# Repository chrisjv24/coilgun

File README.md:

# coilgun
This repository will contain all design files and documentation concerning the Carter X Chris coilgun design.

## Repo Architecture
The repo will be split into the four subsystems of chassis, propulsion, controls, and safety, along with an additional directory for non-technical documents.

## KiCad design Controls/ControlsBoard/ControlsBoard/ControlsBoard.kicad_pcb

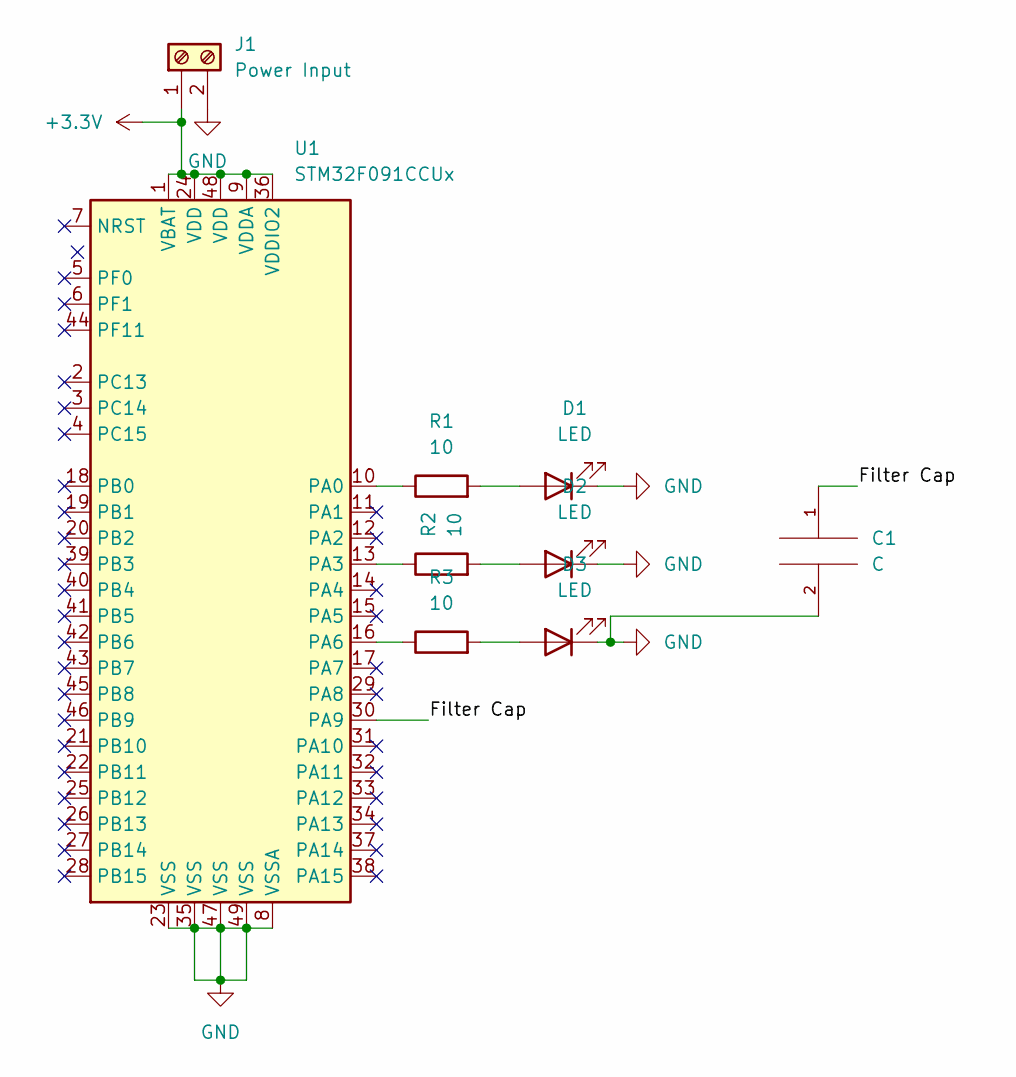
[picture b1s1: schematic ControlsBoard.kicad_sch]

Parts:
C1: C; C_0603_1608Metric
D1, D2, D3: LED; LED_0603_1608Metric
J1: Power Input; TerminalBlock_4Ucon_1x08_P3.50mm_Horizontal
R1, R2: 10; R_0805_2012Metric
R3: 10; R_Axial_DIN0207_L6.3mm_D2.5mm_P2.54mm_Vertical
U1: STM32F091CCUx; QFN-48-1EP_7x7mm_P0.5mm_EP5.6x5.6mm

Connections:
+3.3V: J1.1, U1.1 (VBAT), U1.9 (VDDA), U1.24 (VDD), U1.36 (VDDIO2), U1.48 (VDD)
/Filter Cap: C1.1, U1.30 (PA9)
GND: C1.2, D1.1 (K), D2.1 (K), D3.1 (K), J1.2, U1.8 (VSSA), U1.23 (VSS), U1.35 (VSS), U1.47 (VSS), U1.49 (VSS)
unnamed: D1.2 (A), R1.2
unnamed: D2.2 (A), R2.2
unnamed: D3.2 (A), R3.2
unnamed: R1.1, U1.10 (PA0)
unnamed: R2.1, U1.13 (PA3)
unnamed: R3.1, U1.16 (PA6)

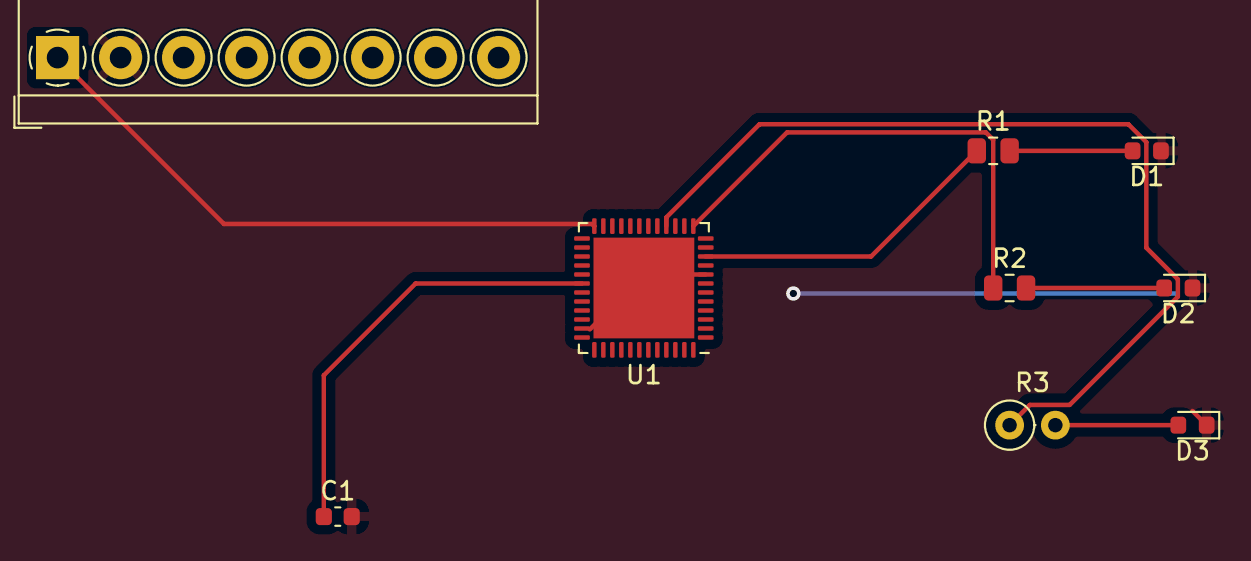
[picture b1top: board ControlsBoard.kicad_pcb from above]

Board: 2 copper layers, 9 parts (0 on the bottom side), 9 nets.

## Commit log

2023-07-20 Added architecture description
2023-07-21 Adding powerpoint and gitignore
2023-07-22 Added Meetings folder
2023-07-22 Added Report
2023-07-22 Added Controls folder and PCB projects
2023-07-22 Added a budget folder and budget Excel sheet
2023-07-22 made a test PCB
2023-07-22 Preliminary design sketch of handle and reload
2023-07-23 Added Chassis Folder
2023-07-23 Added backup folders to .gitignore
2023-07-29 Added PRD
